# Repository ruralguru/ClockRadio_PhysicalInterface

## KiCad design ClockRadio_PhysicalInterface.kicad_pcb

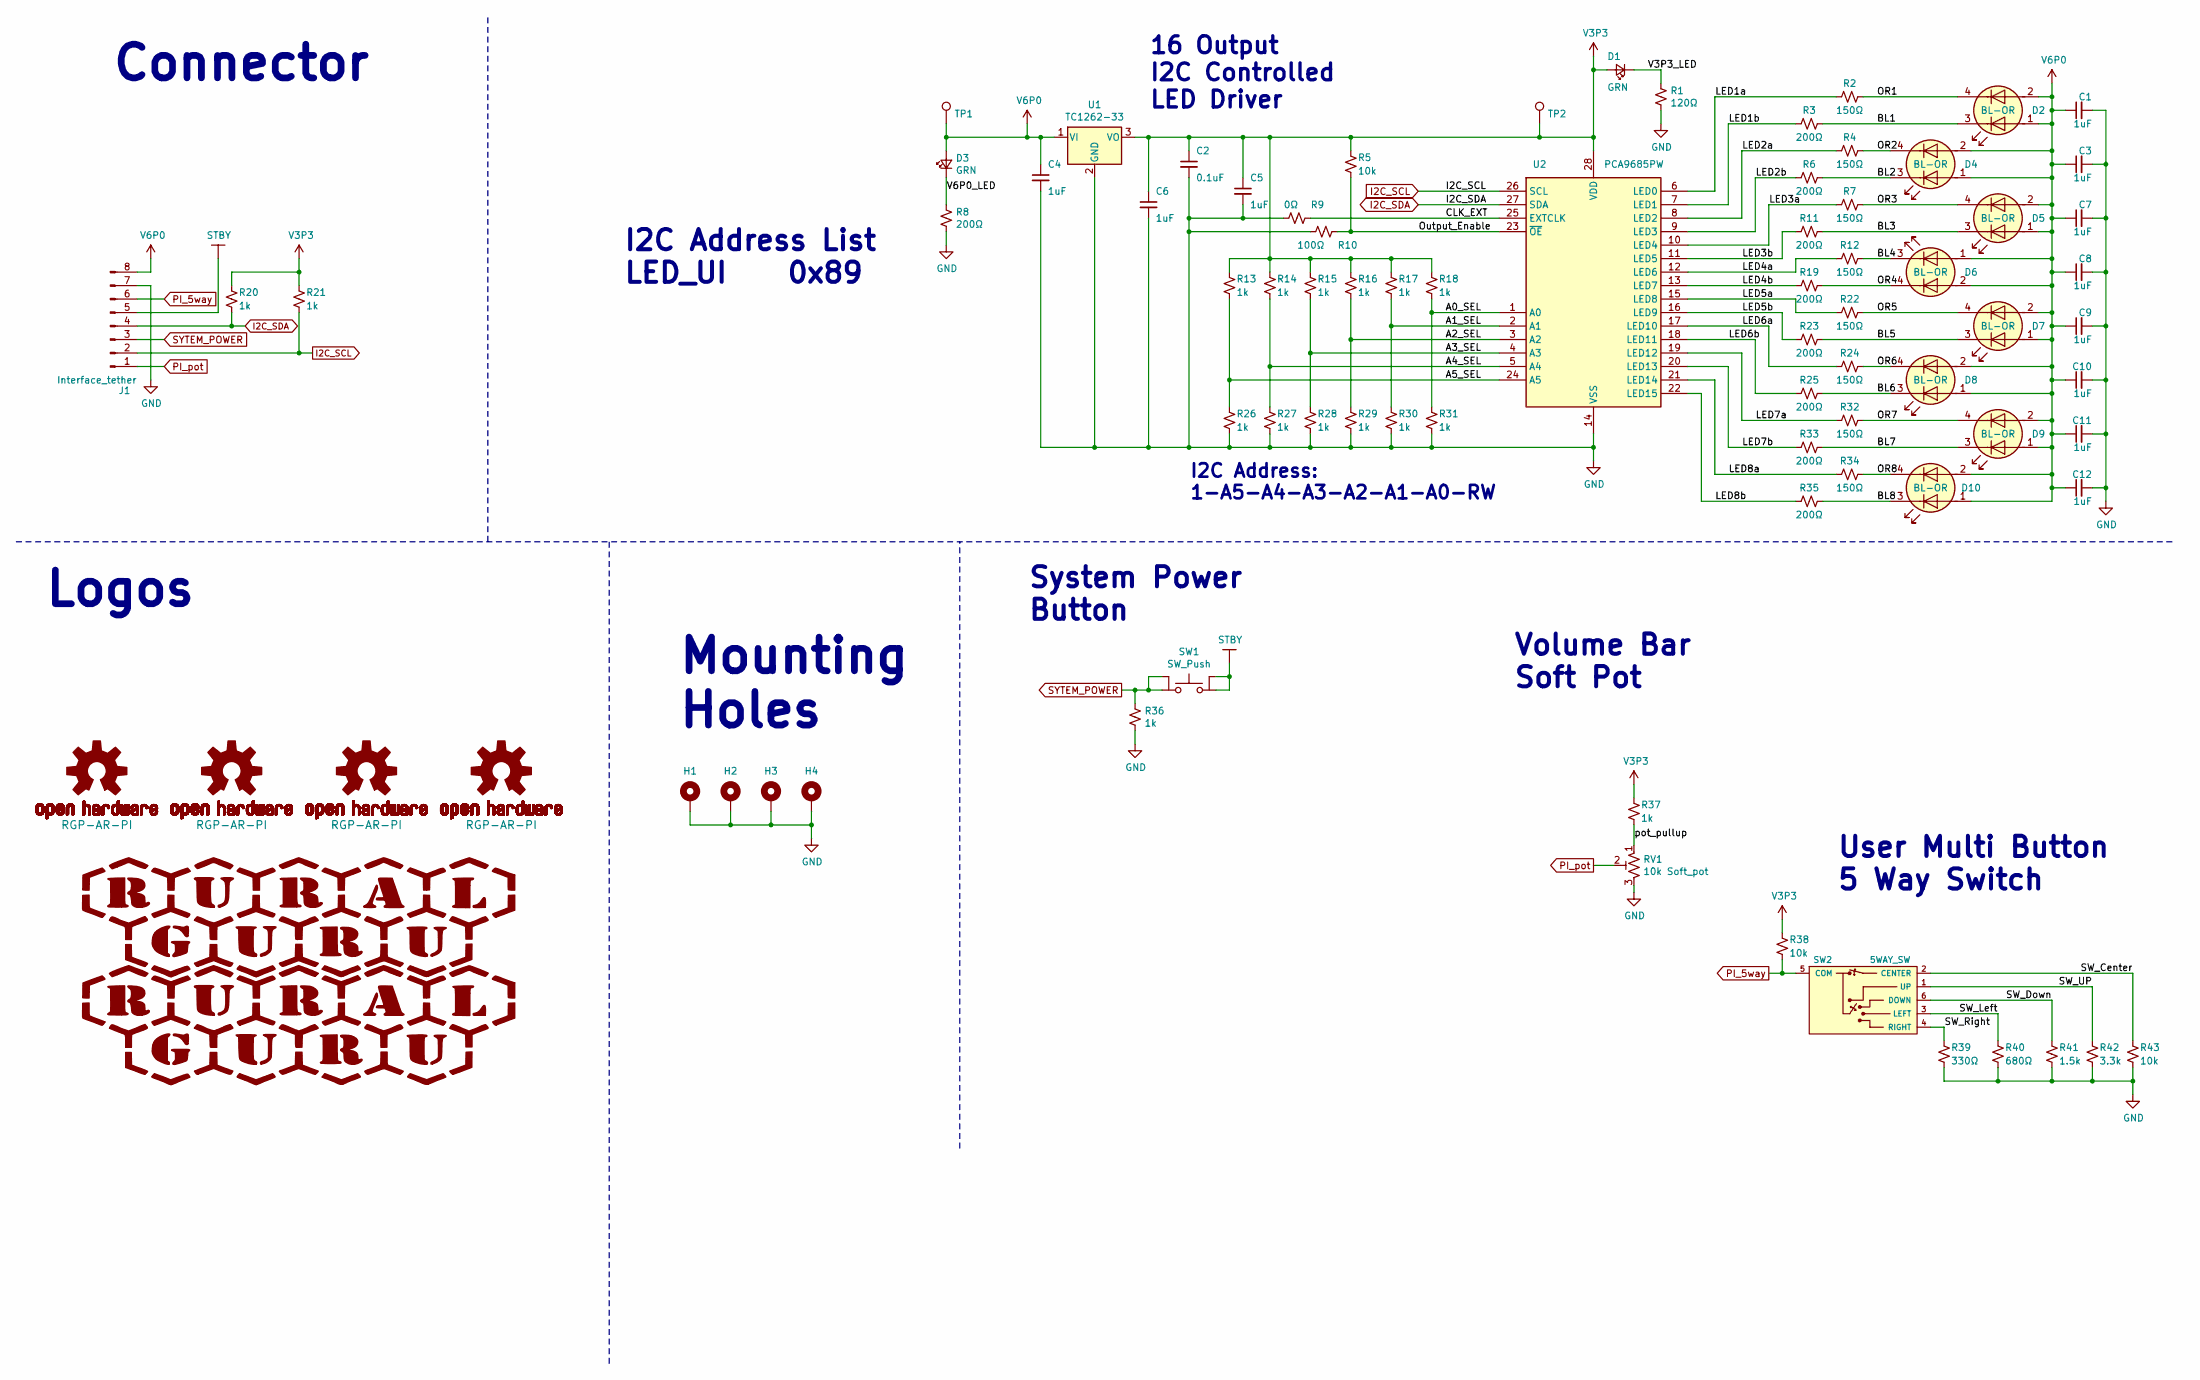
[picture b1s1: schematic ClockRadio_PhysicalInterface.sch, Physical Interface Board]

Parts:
C1, C3, C4, C5, C6, C7, C8, C9, C10, C11, C12: 1uF; C_0603_1608Metric
C2: 0.1uF; C_0603_1608Metric
D1, D3: GRN; LED_0603_1608Metric_Castellated
D2, D4, D5, D6, D7, D8, D9, D10: BL-OR; Double_LED_0603_1608Metric_Castellated
G1, G2: RGP-AR-PI; OSHW-LOGO-L
G3, G4: RGP-AR-PI; OSHW-LOGO-L_COPPER
G5: LOGO; RuralguruProjects_HEX_500
G6: LOGO; RuralguruProjects_HEX_2000
H1, H2, H3, H4: MountingHole_Pad; MountingHole_2.2mm_M2_Pad
J1: Interface_tether; Samtec_TST-104-01-F-D_P2.54mm
R1: 120Ω; R_0603_1608Metric
R2, R4, R7, R12, R22, R24, R32, R34: 150Ω; R_0603_1608Metric
R3, R6, R8, R11, R19, R23, R25, R33, R35: 200Ω; R_0603_1608Metric
R5, R38, R43: 10k; R_0603_1608Metric
R9: 0Ω; R_0603_1608Metric
R10: 100Ω; R_0603_1608Metric
R13, R14, R15, R16, R17, R18, R20, R21, R26, R27, R28, R29, R30, R31, R36, R37: 1k; R_0603_1608Metric
R39: 330Ω; R_0603_1608Metric
R40: 680Ω; R_0603_1608Metric
R41: 1.5k; R_0603_1608Metric
R42: 3.3k; R_0603_1608Metric
RV1: 10k Soft_pot; SW_softpot_100mm
SW1: SW_Push; SW_nano_SMT
SW2: 5WAY_SW; 5way_tactile
TP1, TP2: TestPoint; TestPoint_Pad_D2.0mm
U1: TC1262-33; SOT-223-3_TabPin2
U2: PCA9685PW; TSSOP-28_4.4x9.7mm_P0.65mm

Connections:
/A0_SEL: R18.2, R31.1, U2.1 (A0)
/A1_SEL: R17.2, R30.1, U2.2 (A1)
/A2_SEL: R16.2, R29.1, U2.3 (A2)
/A3_SEL: R15.2, R28.1, U2.4 (A3)
/A4_SEL: R14.2, R27.1, U2.5 (A4)
/A5_SEL: R13.2, R26.1, U2.24 (A5)
/BL1: D2.3 (K1), R3.1
/BL2: D4.3 (K1), R6.1
/BL3: D5.3 (K1), R11.1
/BL4: D6.3 (K1), R12.1
/BL5: D7.3 (K1), R23.1
/BL6: D8.3 (K1), R25.1
/BL7: D9.3 (K1), R33.1
/BL8: D10.3 (K1), R35.1
/CLK_EXT: R9.1, U2.25 (EXTCLK)
/LED1a: R2.2, U2.6 (LED0)
/LED1b: R3.2, U2.7 (LED1)
/LED2a: R4.2, U2.8 (LED2)
/LED2b: R6.2, U2.9 (LED3)
/LED3a: R7.2, U2.10 (LED4)
/LED3b: R11.2, U2.11 (LED5)
/LED4a: R12.2, U2.12 (LED6)
/LED4b: R19.2, U2.13 (LED7)
/LED5a: R22.2, U2.15 (LED8)
/LED5b: R23.2, U2.16 (LED9)
/LED6a: R24.2, U2.17 (LED10)
/LED6b: R25.2, U2.18 (LED11)
/LED7a: R32.2, U2.19 (LED12)
/LED7b: R33.2, U2.20 (LED13)
/LED8a: R34.2, U2.21 (LED14)
/LED8b: R35.2, U2.22 (LED15)
/OR1: D2.4 (K2), R2.1
/OR2: D4.4 (K2), R4.1
/OR3: D5.4 (K2), R7.1
/OR4: D6.4 (K2), R19.1
/OR5: D7.4 (K2), R22.1
/OR6: D8.4 (K2), R24.1
/OR7: D9.4 (K2), R32.1
/OR8: D10.4 (K2), R34.1
/Output_Enable: R5.2, R10.1, U2.23 (~OE)
/SW_Center: R43.1, SW2.2 (CENTER)
/SW_Down: R41.1, SW2.6 (DOWN)
/SW_Left: R40.1, SW2.3 (LEFT)
/SW_Right: R39.1, SW2.4 (RIGHT)
/SW_UP: R42.1, SW2.1 (UP)
/V3P3_LED: D1.1 (K), R1.1
/V6P0_LED: D3.1 (K), R8.1
/pot_pullup: R37.2, RV1.1
GND: C1.2, C2.2, C3.2, C4.2, C5.2, C6.2, C7.2, C8.2, C9.2, C10.2, C11.2, C12.2, H1.1, H2.1, H3.1, H4.1, J1.7, R1.2, R8.2, R9.2, R10.2, R26.2, R27.2, R28.2, R29.2, R30.2, R31.2, R36.2, R39.2, R40.2, R41.2, R42.2, R43.2, RV1.3, U1.2 (GND), U2.14 (VSS)
I2C_SCL: J1.2, R21.2, U2.26 (SCL)
I2C_SDA: J1.4, R20.2, U2.27 (SDA)
PI_5way: J1.6, R38.2, SW2.5 (COM)
PI_pot: J1.1, RV1.2
STBY: J1.5, SW1.3, SW1.4
SYTEM_POWER: J1.3, R36.1, SW1.1, SW1.2
V3P3: C2.1, C5.1, C6.1, D1.2 (A), R5.1, R13.1, R14.1, R15.1, R16.1, R17.1, R18.1, R20.1, R21.1, R37.1, R38.1, TP2.1, U1.3 (VO), U2.28 (VDD)
V6P0: C1.1, C3.1, C4.1, C7.1, C8.1, C9.1, C10.1, C11.1, C12.1, D2.1 (A1), D2.2 (A2), D3.2 (A), D4.1 (A1), D4.2 (A2), D5.1 (A1), D5.2 (A2), D6.1 (A1), D6.2 (A2), D7.1 (A1), D7.2 (A2), D8.1 (A1), D8.2 (A2), D9.1 (A1), D9.2 (A2), D10.1 (A1), D10.2 (A2), J1.8, TP1.1, U1.1 (VI)

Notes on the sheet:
16 Output I2C Controlled LED Driver
I2C Address: 1-A5-A4-A3-A2-A1-A0-RW
Mounting Holes
Logos
I2C Address List LED_UI 0x89
Connector
System Power Button
Volume Bar Soft Pot
User Multi Button 5 Way Switch

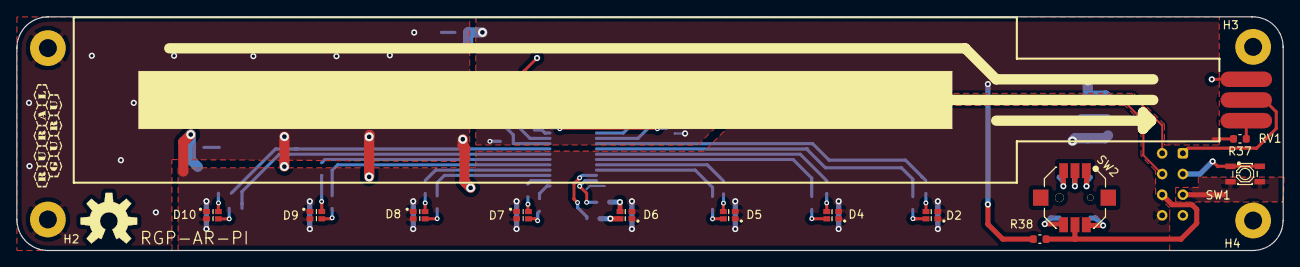
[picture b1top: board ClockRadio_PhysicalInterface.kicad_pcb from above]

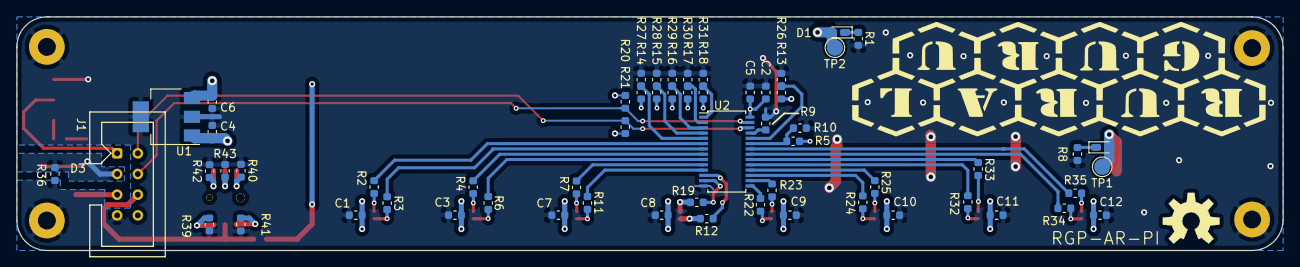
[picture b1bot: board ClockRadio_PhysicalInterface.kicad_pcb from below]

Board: 2 copper layers, 155.6 x 28.7 mm, 83 parts (63 on the bottom side), 57 nets.

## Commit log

2019-06-01 Initial Data Commit. block diagram done, Schematic done, BOM in progress, layout done.
2019-07-13 Schematic and layout complete
